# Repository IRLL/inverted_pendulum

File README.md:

Inverted-Pendulum
=================

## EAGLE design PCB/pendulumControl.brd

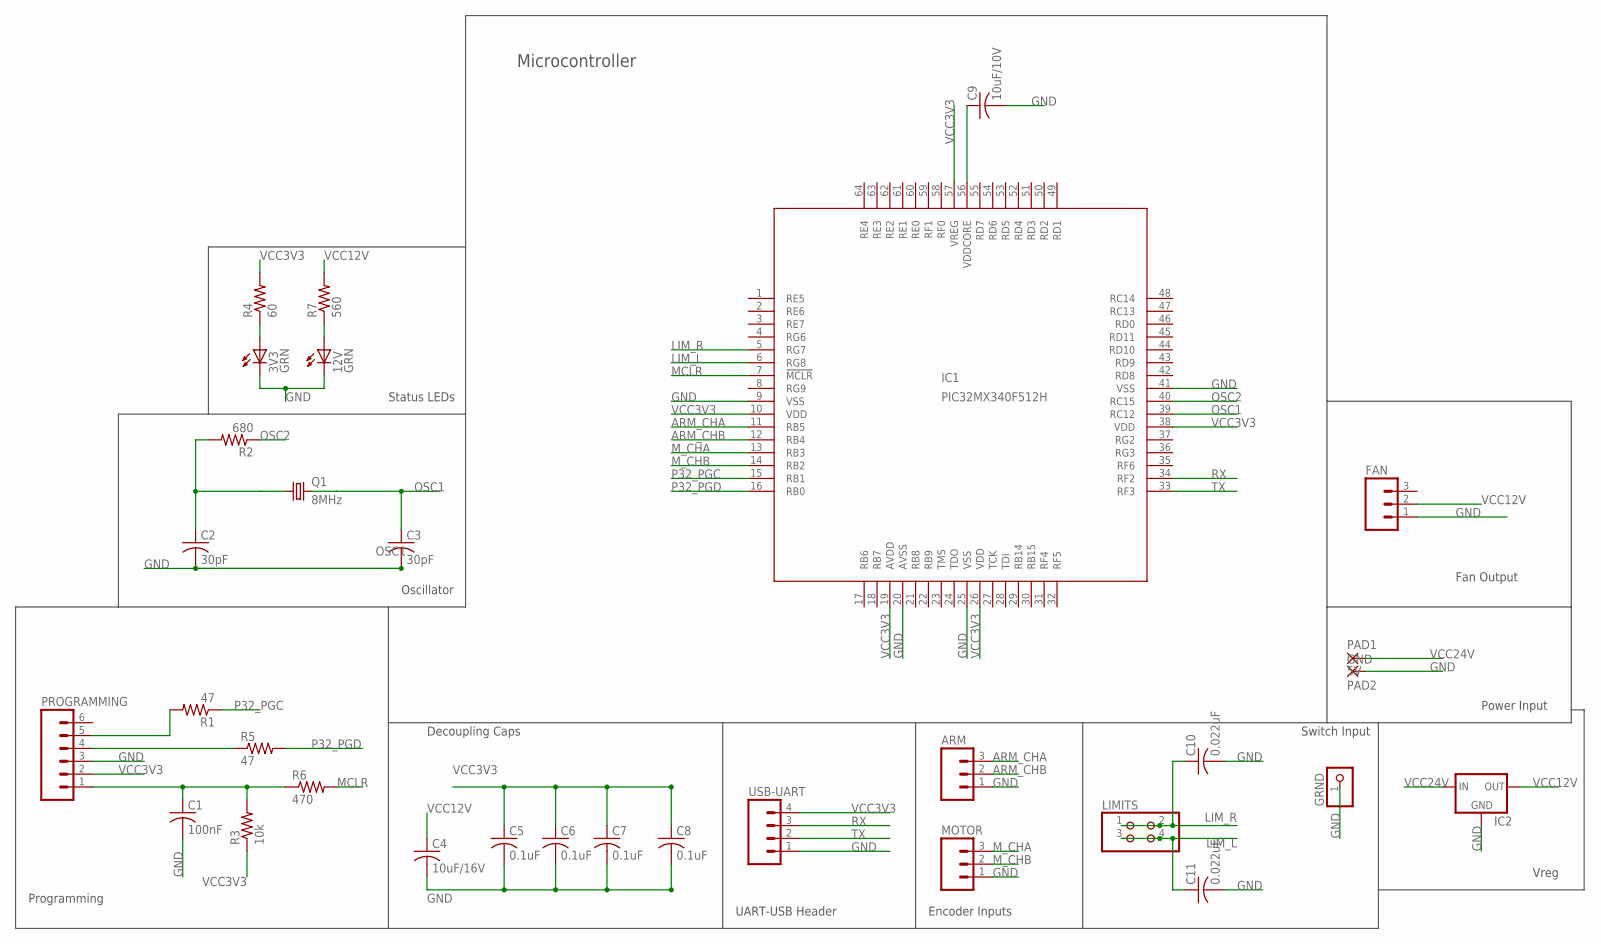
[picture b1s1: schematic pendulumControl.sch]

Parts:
3V3, 12V: GRN; CHIP-LED0805
ARM: M03PTH; 1X03
C1: 100nF; C0805
C2, C3: 30pF; C0805
C4: 10uF/16V; C0805
C5, C6, C7, C8: 0.1uF; C0805
C9: 10uF/10V; C0805
C10, C11: 0.022uF; C0805
FAN: M03POLAR; MOLEX-1X3
GRND: PINHD-1X1; 1X01
IC1: PIC32MX340F512H; TQFP64-10X10
IC2: 78MXXS
LIMITS: PINHD-2X2; 2X02
MOTOR: M03PTH; 1X03
PAD1: 5V; 3,81/1,4
PAD2: GND; 3,81/1,4
PROGRAMMING: M06FEMALE_LOCK; 1X06_FEMALE_LOCK.010
Q1: 8MHz; HC49/S
R1, R5: 47; R0805
R2: 680; R0805
R3: 10k; R0805
R4: 60; R0805
R6: 470; R0805
R7: 560; R0805
USB-UART: M04PTH; 1X04

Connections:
ARM_CHA: ARM.3, IC1.11 (RB5)
ARM_CHB: ARM.2, IC1.12 (RB4)
GND: 3V3.C, 12V.C, ARM.1, C1.2, C2.2, C3.2, C4.2, C5.2, C6.2, C7.2, C8.2, C9.2, C10.2, C11.2, FAN.1, GRND.1, IC1.9 (VSS), IC1.20 (AVSS), IC1.25 (VSS), IC1.41 (VSS), IC2.GND, MOTOR.1, PAD2.1, PROGRAMMING.3, USB-UART.1
LIM_L: C11.1, IC1.6 (RG8), LIMITS.3, LIMITS.4
LIM_R: C10.1, IC1.5 (RG7), LIMITS.1, LIMITS.2
MCLR: IC1.7 (!MCLR), R6.2
M_CHA: IC1.13 (RB3), MOTOR.3
M_CHB: IC1.14 (RB2), MOTOR.2
unnamed: PROGRAMMING.4, R5.1
unnamed: PROGRAMMING.5, R1.2
unnamed: C2.1, Q1.1, R2.2
unnamed: 3V3.A, R4.1
unnamed: 12V.A, R7.1
unnamed: C1.1, PROGRAMMING.1, R3.2, R6.1
unnamed: C9.1, IC1.56 (VDDCORE)
OSC1: C3.1, IC1.39 (RC12), Q1.2
OSC2: IC1.40 (RC15), R2.1
P32_PGC: IC1.15 (RB1), R1.1
P32_PGD: IC1.16 (RB0), R5.2
RX: IC1.34 (RF2), USB-UART.3
TX: IC1.33 (RF3), USB-UART.2
VCC3V3: C5.1, C6.1, C7.1, C8.1, IC1.10 (VDD), IC1.19 (AVDD), IC1.26 (VDD), IC1.38 (VDD), IC1.57 (VREG), PROGRAMMING.2, R3.1, R4.2, USB-UART.4
VCC12V: C4.1, FAN.2, IC2.OUT, R7.2
VCC24V: IC2.IN, PAD1.1

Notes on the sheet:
Programming
Decoupling Caps
Oscillator
UART-USB Header
Encoder Inputs
Switch Input
Microcontroller
Status LEDs
Power Input
Vreg
Fan Output

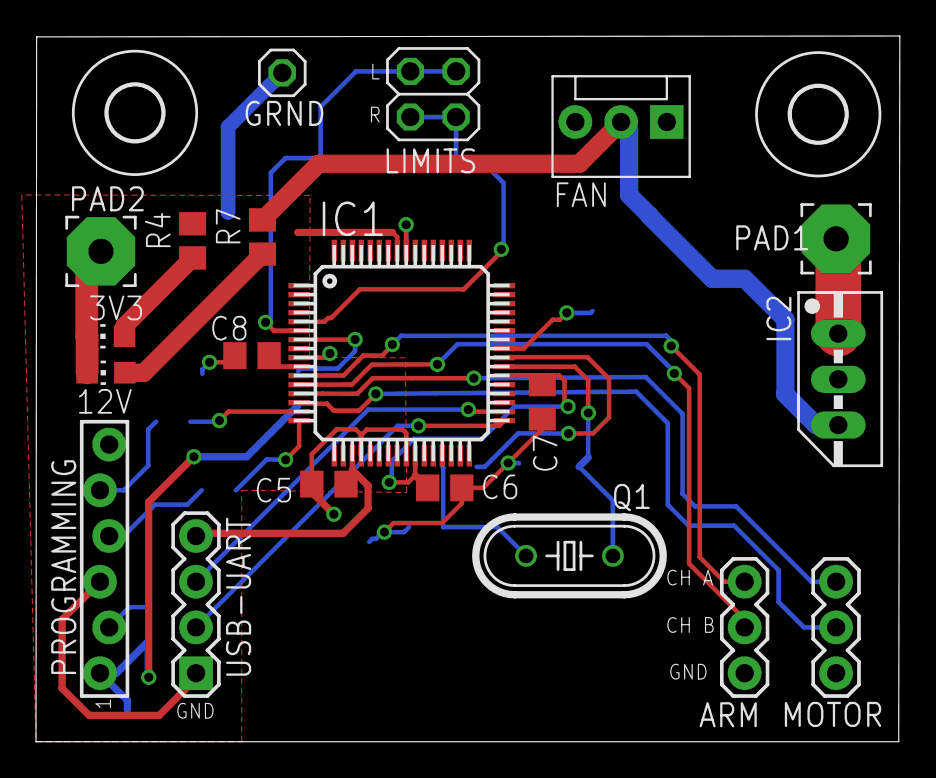
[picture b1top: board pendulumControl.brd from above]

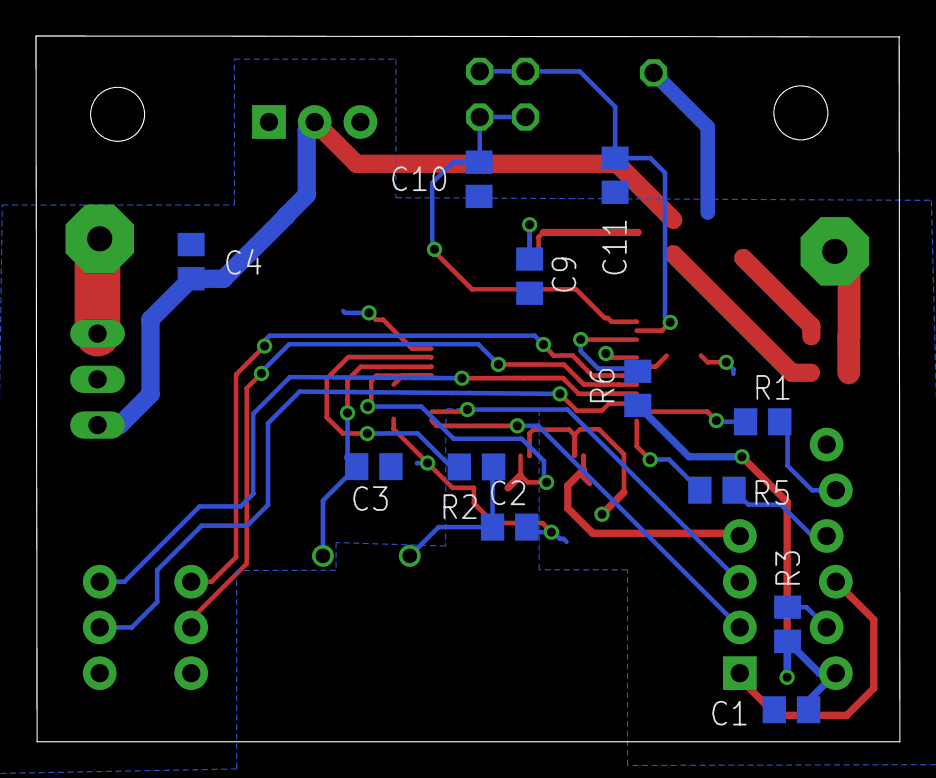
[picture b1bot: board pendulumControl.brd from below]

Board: 2 copper layers, 48.0 x 39.2 mm, 34 parts (12 on the bottom side), 24 nets.

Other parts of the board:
U$1, U$2: 3,0

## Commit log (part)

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2014-10-25 Basic Test for the Stepper Motor
    Requires the AccelStepper library
2014-10-25 Added .git files
2014-11-05 Converted to Arduino
    Due to problems running on a ChipKit we had to convert to using an
    Arduino.
2014-11-07 Added libraries
2014-11-14 Added Detail to Needs
2015-01-21 Preparing for New Setup Testing
2015-01-30 started mplab microcontroller stuff
2015-01-30 set the CN ports
2015-01-30 added queue and UART files
2015-01-30 Started to initialize the UART channels
2015-02-01 Did more UART work and started HTML documentation
2015-02-01 Updated the documentation with information on how optical encoders and the motor controller work
2015-02-02 Added more information to the documentation
2015-02-02 Added reference documents
2015-02-02 Added the UART documentation and updated the overall documentation
2015-02-04 Tried to fix UART and wrote basic __ISR
2015-02-05 Started computer API
2015-02-05 created reader debugging program and port loopback program
2015-02-06 added semaphore code
2015-02-06 "Fixed" UART
2015-02-06 motor forward, backwards, stop control working
2015-02-07 Moved Images to the gh-pages images folder
2015-02-07 Updated .gitignore and moved images
2015-02-07 Moved documents to the gh-pages branch
2015-02-07 Updated index
2015-02-09 Removed the unnecessary images folder from this branch
2015-02-09 Uploaded Bootstrap for future use
2015-02-11 some threading, added variable reading functions
    this is just a proof-of-concept right now, eventually variables should
    get stored as class variables, and the read functions should pull from
    there, and the motor variable process should populate the values
2015-02-11 started moving motor controller to its own class
2015-02-12 finished motor class
    also integrated new class with pendulum library
2015-02-12 Updated to Bootstrap Page
2015-02-12 Fixed Image sizes on mobile
2015-02-12 Made images responsive
2015-02-13 partially working microcontroller
    looks like it might be a timing issue with the UART, we may need to use crystal oscillator for its more accurate clock
2015-02-13 Removed Google Analytics Code
2015-02-13 Removed Blog button
2015-02-13 Started Software Flowchart
2015-02-14 Hopefully fixed oscillator problems
2015-02-16 Added uc_interface into the Pendulum.py
2015-02-16 Added reference to the Pendulum class to get the variables
2015-02-17 working microcontroller (I think)
    upped UART rate to 2MHz
    set analog pins to digital mode (that's what was messing up the encoders)
    added timer stuff (commented out)
2015-02-17 microcontroller now running at 80MHz
2015-02-20 Added Theory on the encoders
2015-02-20 Switched the Encoder Channels
2015-02-20 Built the Encoder Class
2015-02-23 Removed CN section and updated UART
2015-02-25 Started Qt GUI development
2015-02-25 Finished Work on GUI
2015-02-26 Updated the print stats function to output to the GUI
2015-02-26 Fixed Typo
2015-02-26 Fixed a few tab issues
2015-02-27 Fixed Bugs
2015-03-02 Did more GUI work
2015-03-09 Removed GUI for ease of coding and removed UART2
2015-03-09 Added basic Packeting for UART
2015-03-09 Made all variables global
2015-03-10 added python profiler script
2015-03-11 fixed bug in encoder logic
2015-03-11 modded uc_interface to work with new microcontroller code
    need to calibrate rotation constants
    also need to mod microcontroller code to wrap around high and negative values
2015-03-12 working on increasing microcontroller efficiency and reset/initialization
2015-03-12 working on sleeping before reset
2015-03-12 working reset and values are calibrated
2015-03-13 changes to reset and printing
2015-03-17 removed old/unused functions and variables
2015-03-17 modified the reset wait logic this should reduce the chances of a false positive occuring
2015-03-19 tweak for uart ISR to run faster
2015-03-19 tabular Sarsa completed, not tested
2015-03-19 Added some more BOM info
2015-03-19 Updated .gitignore
2015-03-28 microcontroller changes
    some cleanup, also modded code for pendulum resetting to the right instead of the left
2015-03-28 made uc_interface executable, added motor tester
2015-05-02 Started work on the PCB design
2015-05-04 Added oscillator
2015-05-04 Completed first routing.
2015-05-12 Fixed Header on wrong side of board
2015-05-13 Started the setup routine
2015-05-13 Finished setup.py for now
2015-05-16 Possibly made _ISR faster
2015-05-18 Added Mounting Holes. Updated the setup.
2015-05-19 Fixed Tab issues and made Setup into a class
2015-05-19 Fixed some small errors
2015-05-19 Finally fixed Tabs
2015-05-20 Added in a watchdog thread for the software braking system
    Need to check logic/validity in context
2015-05-20 Fixed MPLAB X ignores
2015-05-21 1st attempt at UART optimization.
2015-05-21 Fixed build errors and added Encoder lookup table.
2015-05-21 Fixed small bugs
2015-05-21 Reverted back to working microcontroller code
2015-05-22 Added Lookup Table logic
2015-05-22 Attempted to optimize UART transmission
2015-05-22 Removed Call to UART1 RX callback
2015-05-22 Comment out UART 1 Handler ISR
2015-05-23 Started to make parts list for PCB
2015-05-23 Fixed last bugs in the microcontroller optimizations
2015-05-26 Added required constants and added parts to parts list
2015-05-26 Attempt to fix div by 0
2015-05-26 Fixed div by 0 error
2015-05-26 Added code for handling 0 crossover
2015-05-27 Finished BOM and moved oscillator closer to the microcontroller
2015-05-27 Changed angular velocity calculation
2015-05-27 Removed excess print statements
2015-05-27 Added ROS gitignore
2015-05-27 Squashed some more bugs, still problems
2015-05-27 Added ROS vision processing
2015-05-27 ROS vision processing
2015-05-28 gitignore updated
2015-05-28 Fixed tester calls for moving left and right.
2015-05-29 Getting ready to remove some parts
2015-06-01 Updated the PCB
2015-06-03 Added smoothing caps to the limit switches.
2015-06-04 Board update
2015-06-04 Fix conflicts
2015-06-05 Board is finalized and checked
2015-06-08 some small tweaks to breaking
2015-06-10 Started code cleanup. Moved all testing functions to separate script called testing.py with menu system.
2015-06-11 Made some small changes to testing UI
2015-06-15 vision
2015-06-15 policy gradient implemented, not tested
2015-06-15 fixed error
2015-06-16 Added getDegrees and modified watchdog to wait for reset. Also added velocity into the state space.
2015-06-16 Small fixes
2015-06-16 Fixed a small bug and did testing
2015-08-03 committed Gabe's changes
2015-08-04 removed score plotting, added angle plotting
2015-08-06 added timing calculations
2015-08-06 Moved timing code to correct place
2015-08-07 Added code for dynamic sleeping. Will make the trajectory loop run at a constant speed.
2015-08-07 Dynamic sleeping is working
2015-09-21 Prepared for Simulation
2015-09-22 started splitting simulator into functional pieces
2015-09-22 working on pend_sim.py
2015-09-23 removed all crud from simulator, still needs cleanup
2015-09-23 added tester of simulator with visualization
2015-09-23 started adding friction to the physics model
2015-09-29 simulator close to finished, friction still causing issues
2015-10-01 lots of fixes and improvements, just small tweaks and extra features to be added
    physics model is working
    frame rate updates working
    lots of command line parameters
    probably just need to add more agent functions now, like init
2015-10-01 Style changes.
2015-10-07 Added performance reporting for random agent.
2015-10-07 First pass at Sarsa with NN - Not learning.
2015-10-08 added screen saving, edge detection, and shortened track
2015-10-08 fixed bugs I created
2015-10-09 First pass at tabular sarsa(λ).
2015-10-09 Variable feature resolution and tie breaking.
    Each feature's resolution can be adjusted as necessary as the third value in the
    bounds.
    Action selection was always going left due to how all actions being equal, it
    would pick the first option. Now it will tie break randomly.
2015-10-15 gui now displays text readout for angle and position
2015-10-15 shifted track 0 to center
2015-10-15 fixed pendulum angle
    angle is now reported from -pi to +pi, with zero being vertical
2015-10-19 fixed input angle calculation to be consistent with output angle
2015-10-21 Simulator changes + NFQ work.
2015-10-21 Simple NFQ - Centering - Mostly working.
2015-11-12 Trying out pid controller with limited action set.
2015-11-30 Working visualizer backend.
2015-11-30 DQN runfile for cartpole exp.
2016-03-13 added fail angle logic, fixed some bugs with sarsa agent, added plotting
2016-03-13 promising results
2016-03-13 seems to be close to balancing
2016-03-13 Added the basic framework for the ROS package
2016-03-13 Added Vision CMakeList
2016-03-13 Created the package to use.
2016-03-20 Added base files to the package
2016-03-20 Filled out basic pub/sub for each module
2016-03-20 moved python to the scripts folder
2016-03-22 Added PendulumPose message type and removed space from folder name
2016-03-24 Added custom messages and started the MotorSerial node
2016-03-24 Added callback data parsing and printing functionality
2016-03-24 fixed problem with globals
2016-03-24 added fps variable for update rate
2016-03-28 Made command a 64 bit float
2016-04-04 Started making the Motor script into a class
2016-04-19 fixed whitespace
2016-04-23 added adc channel, fixed i2c bug
2016-04-23 started adding model and visualizer to ros package
    a lot of decoupled parameters like track length should probably become rosparams
2016-05-18 Made the Status a class for readability
2016-08-25 tweaked arduino code
    pretty stable now
2016-08-25 added module for converting raw sensors to polished sensor data
2016-08-26 repo cleanup
    removed unneccesary file, fixed file modes
2016-08-26 added keyboard controller
2016-08-26 finished adding simulation parameters
2016-08-26 tweaked x position to be 0-center
2016-08-26 removed text from visualizer
2016-08-27 added pid agent
    still needs tuning
2016-08-27 converted tabs to spaces
2016-08-30 started swingup agent
2016-09-02 added dqn_ros submodule
2016-09-02 removed DQN_Sim, not needed
2016-09-02 modified simulator to run at variable realtime-speed
2016-09-02 added model and visualizer files directly to ROS folders
2016-09-02 removed old files
2016-09-02 remated settings folder to param
2016-09-03 added reset action to pendulum
2016-09-05 reverting rostopic names
2016-09-07 change printing format
2016-09-08 updated motor controller node
    implemented sensor reading and control
    also added timeout to stop the motor when the /cmd topic is stale
2016-09-08 fixed motor bug
    now converting negative values properly
2016-09-08 Started work on improved messages
2016-09-08 Finished expanded messages
2016-09-09 added angle rotation and calibration features
2016-09-09 fixed tabs and permissions on MotorSerial
2016-09-09 Initial conversion to ncurses, needs work
2016-09-09 Fixed most problems, should just be formatting now
2016-09-10 Status Display now has pretty colors
2016-09-14 Fixed padding and truncation of floats.
2016-09-14 started x position sensor processing
2016-09-14 added launchfile and settings file for real inverted pendulum
2016-09-14 tab stuff
2016-09-14 motor controller port now loaded from settings file
2016-09-14 fixed bugs in motor position and limit switches
2016-09-14 tuned pid parameters for location
2016-09-14 changed motor timeout, fixed indent error
2016-09-14 more pid tuning
2016-09-15 change size of the visualizer
2016-09-17 fixed issue when resetting model
2016-10-03 basic safety controller working
    just using brake right now for stopping, mostly works for preventing pendulum from ramming too hard
2016-10-03 updated sim_setting params
2016-10-06 added myself to the maintainers list
2016-10-06 much better safety controller
2016-10-06 fixed whitespace errors
2016-10-06 added rosserial dependency to package
2016-10-07 started velocity fix
    I think the issue is the velocity going to zero when we hit the limit switches
2016-10-11 more work on edge detection, needs testing
2016-10-11 fixed issues with edge detection
2016-10-11 fixed topic on joystick controller
2016-10-13 tweaks for arduino code robustness
    switched to using the WSWire library for more robust i2c, and added watchdog
    timer in case anything goes really wrong.
2016-10-14 fixed status display
2016-12-05 modified angle reading to use analog output instead of i2c

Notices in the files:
parts and their libraries:
SparkFun-Connectors: Licensing: Creative Commons ShareAlike 4.0 International - https://creativecommons.org/licenses/by-sa/4.0
